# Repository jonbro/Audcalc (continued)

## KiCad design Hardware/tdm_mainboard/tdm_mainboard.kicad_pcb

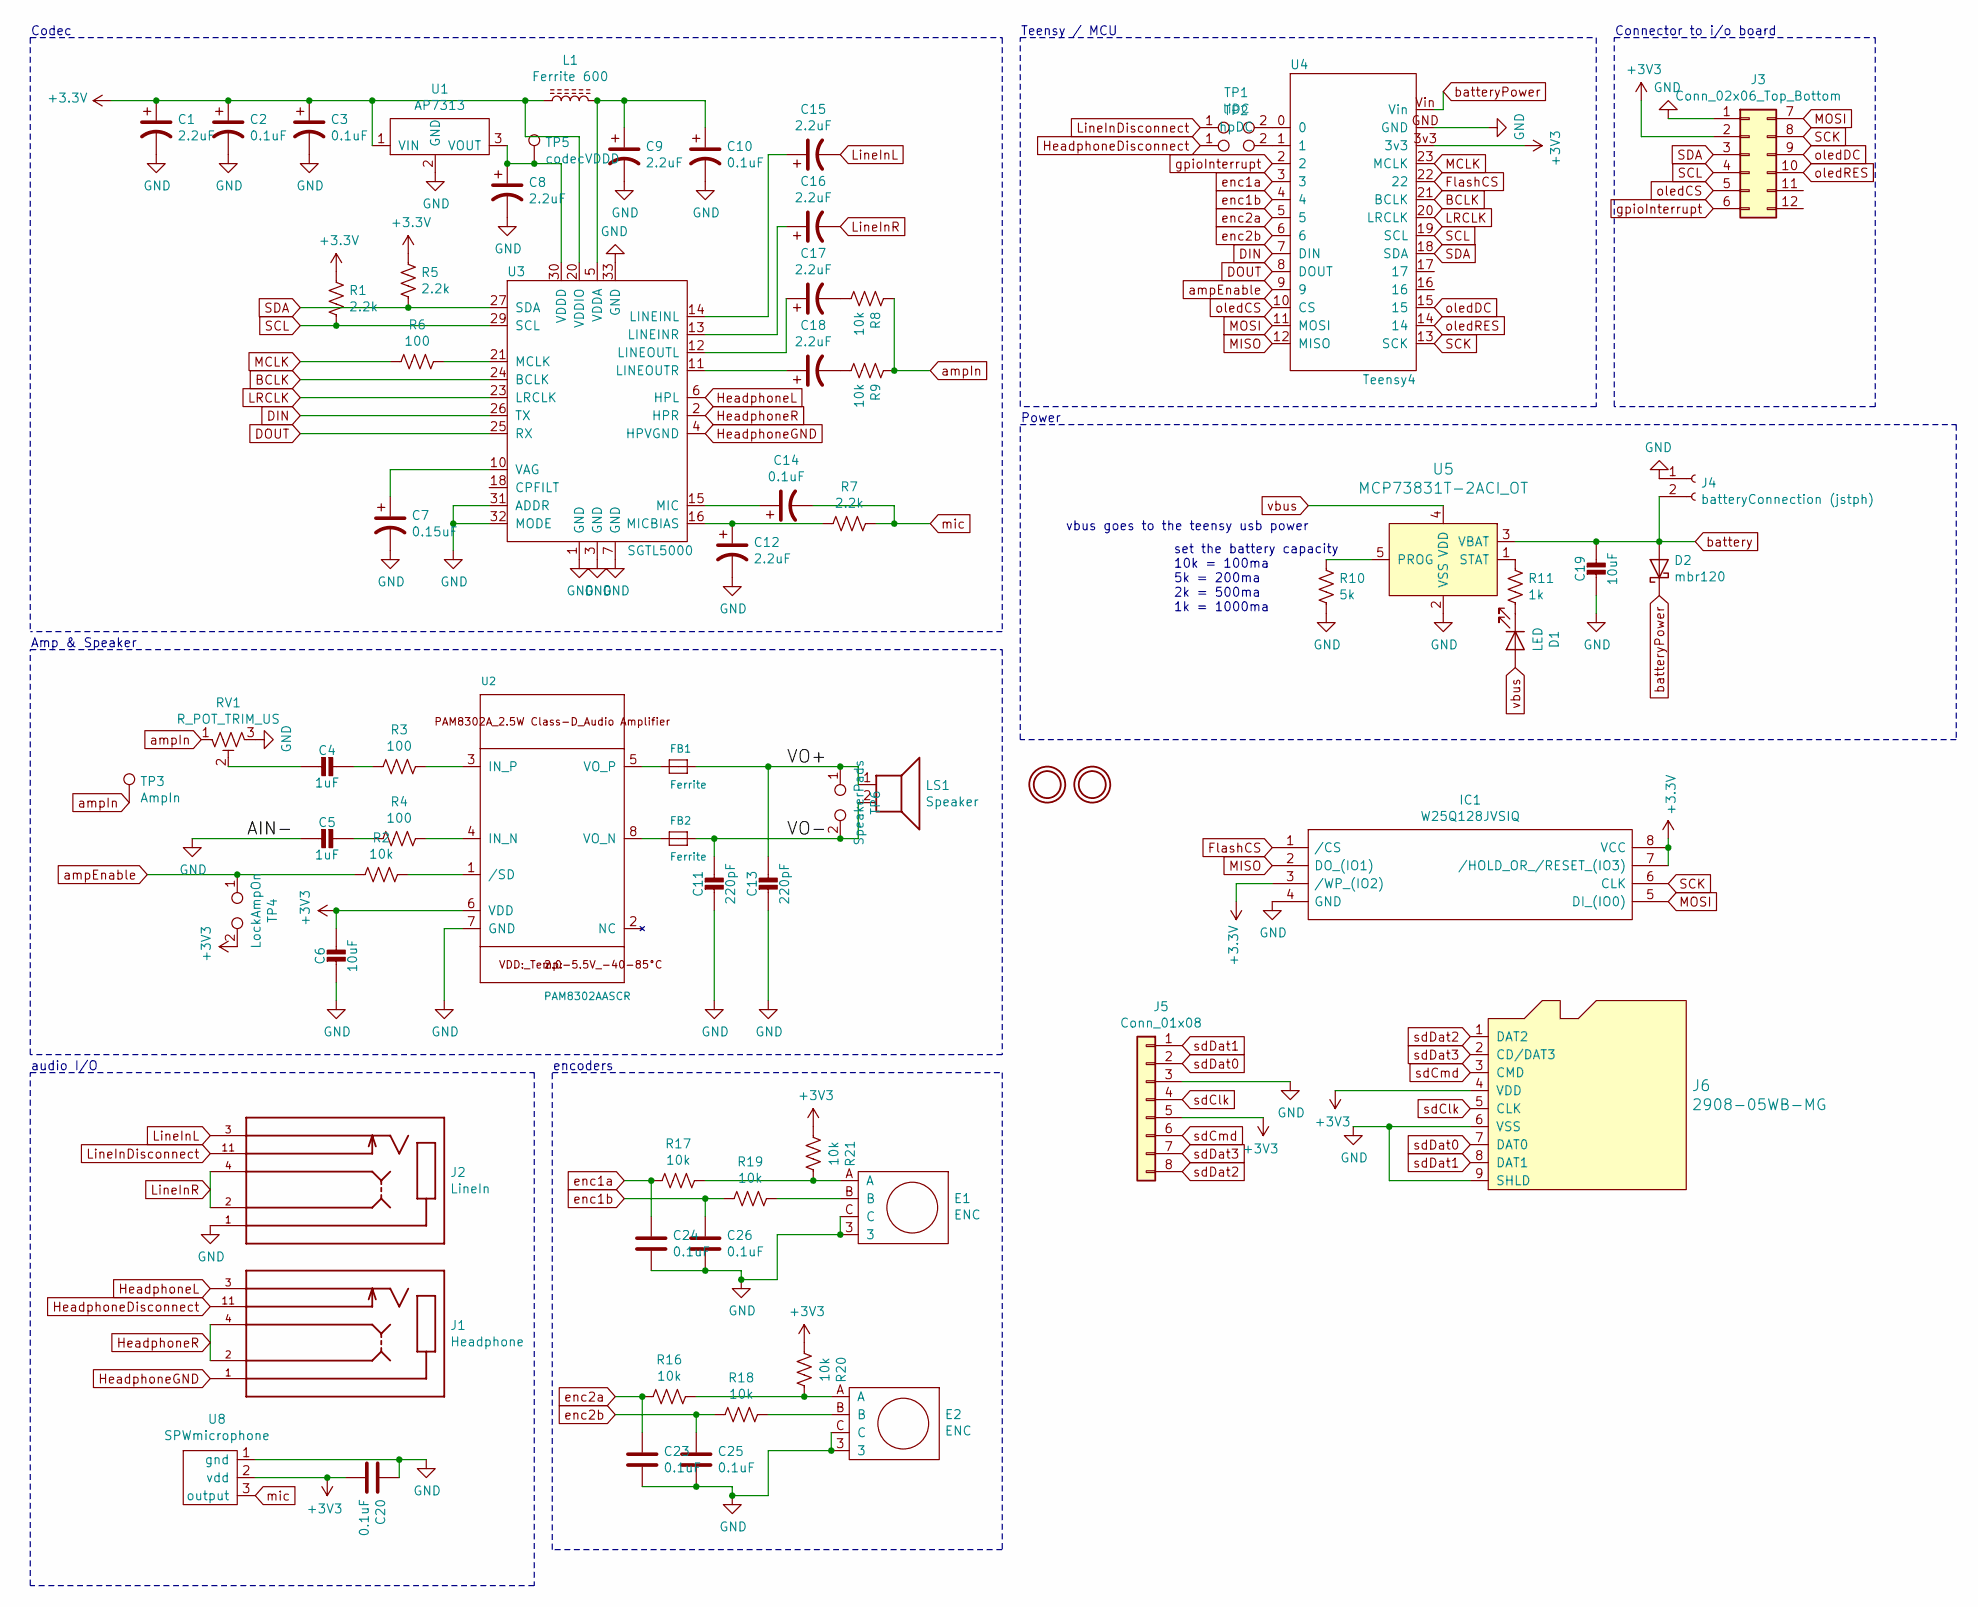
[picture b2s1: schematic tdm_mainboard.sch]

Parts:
C1, C8, C9, C12, C15, C16, C17, C18: 2.2uF; C_0603
C2, C3, C10, C14, C20, C23, C24, C25, C26: 0.1uF; C_0603
C4, C5: 1uF; C_0603
C6, C19: 10uF; C_0603
C7: 0.15uF; C_0603
C11, C13: 220pF; C_0603
D1: LED; LED_0603_HandSoldering
D2: mbr120; D_SOD-123F
E1, E2: ENC; Rotary_Encoder_PEC11R
FB1, FB2: Ferrite; L_0805_HandSoldering
IC1: W25Q128JVSIQ; SOIC127P790X216-8N; Mouser Part Number 454-W25Q128JVSIQ
J1: Headphone; CUI_SJ2-35043C-SMT-TR
J2: LineIn; CUI_SJ2-35043C-SMT-TR
J3: Conn_02x06_Top_Bottom; PinHeader_2x06_P2.54mm_Vertical
J4: batteryConnection (jstph); JST_PH_B2B-PH-K_02x2.00mm_Straight
J5: Conn_01x08; SFW8R-3STE1LF
J6: 2908-05WB-MG; MOLEX_503182-1852_microsd; MPN 2908-05WB-MG; Digi-Key_PN 3M5607CT-ND
L1: Ferrite 600; L_0805_HandSoldering
LS1: Speaker; CMS-18138A-SP
R1, R5, R7: 2.2k; R_0603
R2, R8, R9, R16, R17, R18, R19, R20, R21: 10k; R_0603
R3, R4, R6: 100; R_0603
R10: 5k; R_0603
R11: 1k; R_0603
RV1: R_POT_TRIM_US; TC33X-2_1
TP1: liDC; Test_Point_2Pads
TP2: hpDC; Test_Point_2Pads
TP3: AmpIn; Measurement_Point_Round-TH_Small
TP4: LockAmpOn; Test_Point_2Pads
TP5: codecVDDD; Measurement_Point_Round-SMD-Pad_Small
TP6: SpeakerPads; Test_Point_2Pads
U1: AP7313; SOT-23
U2: PAM8302AASCR; SOP65P490X110-8N
U3: SGTL5000; QFN50P500X500X90-33N
U4: Teensy4
U5: MCP73831T-2ACI_OT; SOT-23-5; MPN MCP73831T-2ACI/OT; Digi-Key_PN MCP73831T-2ACI/OTCT-ND
U6, U7: MOUNTINGHOLE2.5; MountingHole_2.5mm
U8: SPWmicrophone; MIC_SPW2430HR5H-B

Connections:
/VO+: C13.1, FB1.2, LS1.1, TP6.1
/VO-: C11.1, FB2.2, LS1.2, TP6.2
BCLK: U3.24 (BCLK), U4.21 (BCLK)
DIN: U3.26 (TX), U4.7 (DIN)
DOUT: U3.25 (RX), U4.8 (DOUT)
FlashCS: IC1.1 (/CS), U4.22
GND: C1.2, C2.2, C3.2, C5.2, C6.2, C7.2, C8.2, C9.2, C10.2, C11.2, C12.2, C13.2, C19.2, C20.1, C23.2, C24.2, C25.2, C26.2, E1.3, E1.C, E2.3, E2.C, IC1.4 (GND), J2.1 (SLEEVE), J3.1, J4.1, J5.3, J6.6 (VSS), J6.9 (SHLD), R10.2, RV1.3, U1.2 (GND), U2.7 (GND), U3.1 (GND), U3.3 (GND), U3.7 (GND), U3.31 (ADDR), U3.32 (MODE), U3.33 (GND), U4.GND, U5.2 (VSS), U8.1 (gnd)
HeadphoneDisconnect: J1.11 (RING_SWITCH), TP2.1
HeadphoneGND: J1.1 (SLEEVE), U3.4 (HPVGND)
HeadphoneL: J1.3 (RING), U3.6 (HPL)
HeadphoneR: J1.2 (TIP_1), J1.4 (TIP_2), U3.2 (HPR)
LRCLK: U3.23 (LRCLK), U4.20 (LRCLK)
LineInDisconnect: J2.11 (RING_SWITCH), TP1.1
LineInL: C15.2, J2.3 (RING)
LineInR: C16.2, J2.2 (TIP_1), J2.4 (TIP_2)
MCLK: R6.2, U4.23 (MCLK)
MISO: IC1.2 (DO_(IO1)), U4.12 (MISO)
MOSI: IC1.5 (DI_(IO0)), J3.7, U4.11 (MOSI)
unnamed: C4.1, R3.2
unnamed: C4.2, RV1.2
unnamed: C5.1, R4.2
unnamed: C7.1, U3.10 (VAG)
unnamed: C8.1, TP5.1, U1.3 (VOUT), U3.30 (VDDD)
unnamed: C9.1, C10.1, L1.2, U3.5 (VDDA)
unnamed: C12.1, R7.2, U3.16 (MICBIAS)
unnamed: C14.1, U3.15 (MIC)
unnamed: C15.1, U3.14 (LINEINL)
unnamed: C16.1, U3.13 (LINEINR)
unnamed: C17.1, U3.12 (LINEOUTL)
unnamed: C17.2, R8.2
unnamed: C18.1, U3.11 (LINEOUTR)
unnamed: C18.2, R9.2
unnamed: D1.1 (K), R11.2
unnamed: E1.A, R17.1, R21.1
unnamed: E1.B, R19.1
unnamed: E2.A, R16.1, R20.1
unnamed: E2.B, R18.1
unnamed: FB1.1, U2.5 (VO_P)
unnamed: FB2.1, U2.8 (VO_N)
unnamed: R2.1, U2.1 (/SD)
unnamed: R3.1, U2.3 (IN_P)
unnamed: R4.1, U2.4 (IN_N)
unnamed: R6.1, U3.21 (MCLK)
unnamed: R10.1, U5.5 (PROG)
unnamed: R11.1, U5.1 (STAT)
unnamed: TP1.2, U4.0
unnamed: TP2.2, U4.1
SCK: IC1.6 (CLK), J3.8, U4.13 (SCK)
SCL: J3.4, R1.2, U3.29 (SCL), U4.19 (SCL)
SDA: J3.3, R5.2, U3.27 (SDA), U4.18 (SDA)
ampEnable: R2.2, TP4.1, U4.9
ampIn: R8.1, R9.1, RV1.1, TP3.1
battery: C19.1, D2.2 (A), J4.2, U5.3 (VBAT)
batteryPower: D2.1 (K), U4.Vin
enc1a: C24.1, R17.2, U4.3
enc1b: C26.1, R19.2, U4.4
enc2a: C23.1, R16.2, U4.5
enc2b: C25.1, R18.2, U4.6
gpioInterrupt: J3.6, U4.2
mic: C14.2, R7.1, U8.3 (output)
oledCS: J3.5, U4.10 (CS)
oledDC: J3.9, U4.15
oledRES: J3.10, U4.14
sdClk: J5.4, J6.5 (CLK)
sdCmd: J5.6, J6.3 (CMD)
sdDat0: J5.2, J6.7 (DAT0)
sdDat1: J5.1, J6.8 (DAT1)
sdDat2: J5.8, J6.1 (DAT2)
sdDat3: J5.7, J6.2 (CD/DAT3)
vbus: D1.2 (A), U5.4 (VDD)

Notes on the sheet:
Power
Amp & Speaker
Codec
audio I/O
encoders
Teensy / MCU
Connector to i/o board
vbus goes to the teensy usb power
set the battery capacity 10k = 100ma 5k = 200ma 2k = 500ma 1k = 1000ma

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
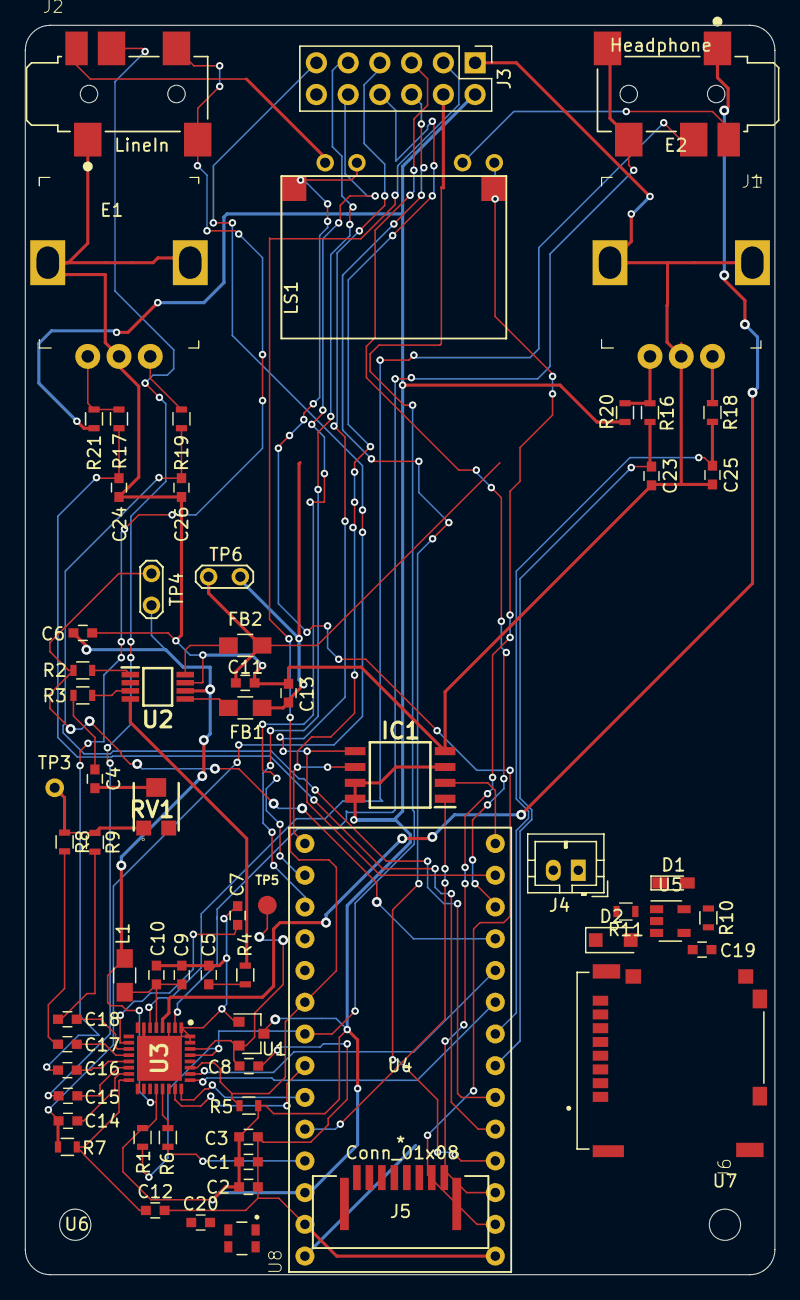
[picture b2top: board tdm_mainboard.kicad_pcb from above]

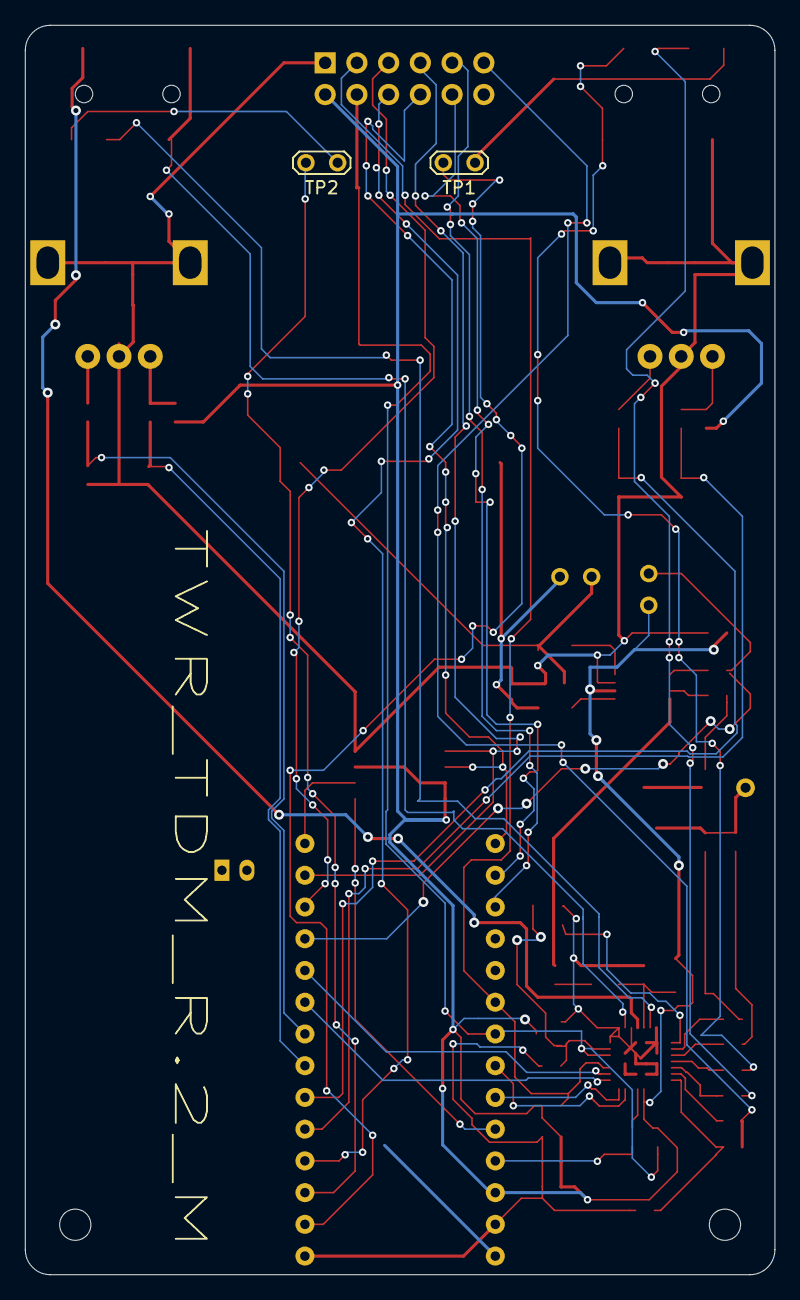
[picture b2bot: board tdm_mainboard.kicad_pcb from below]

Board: 2 copper layers, 60.0 x 100.0 mm, 71 parts (2 on the bottom side), 71 nets.

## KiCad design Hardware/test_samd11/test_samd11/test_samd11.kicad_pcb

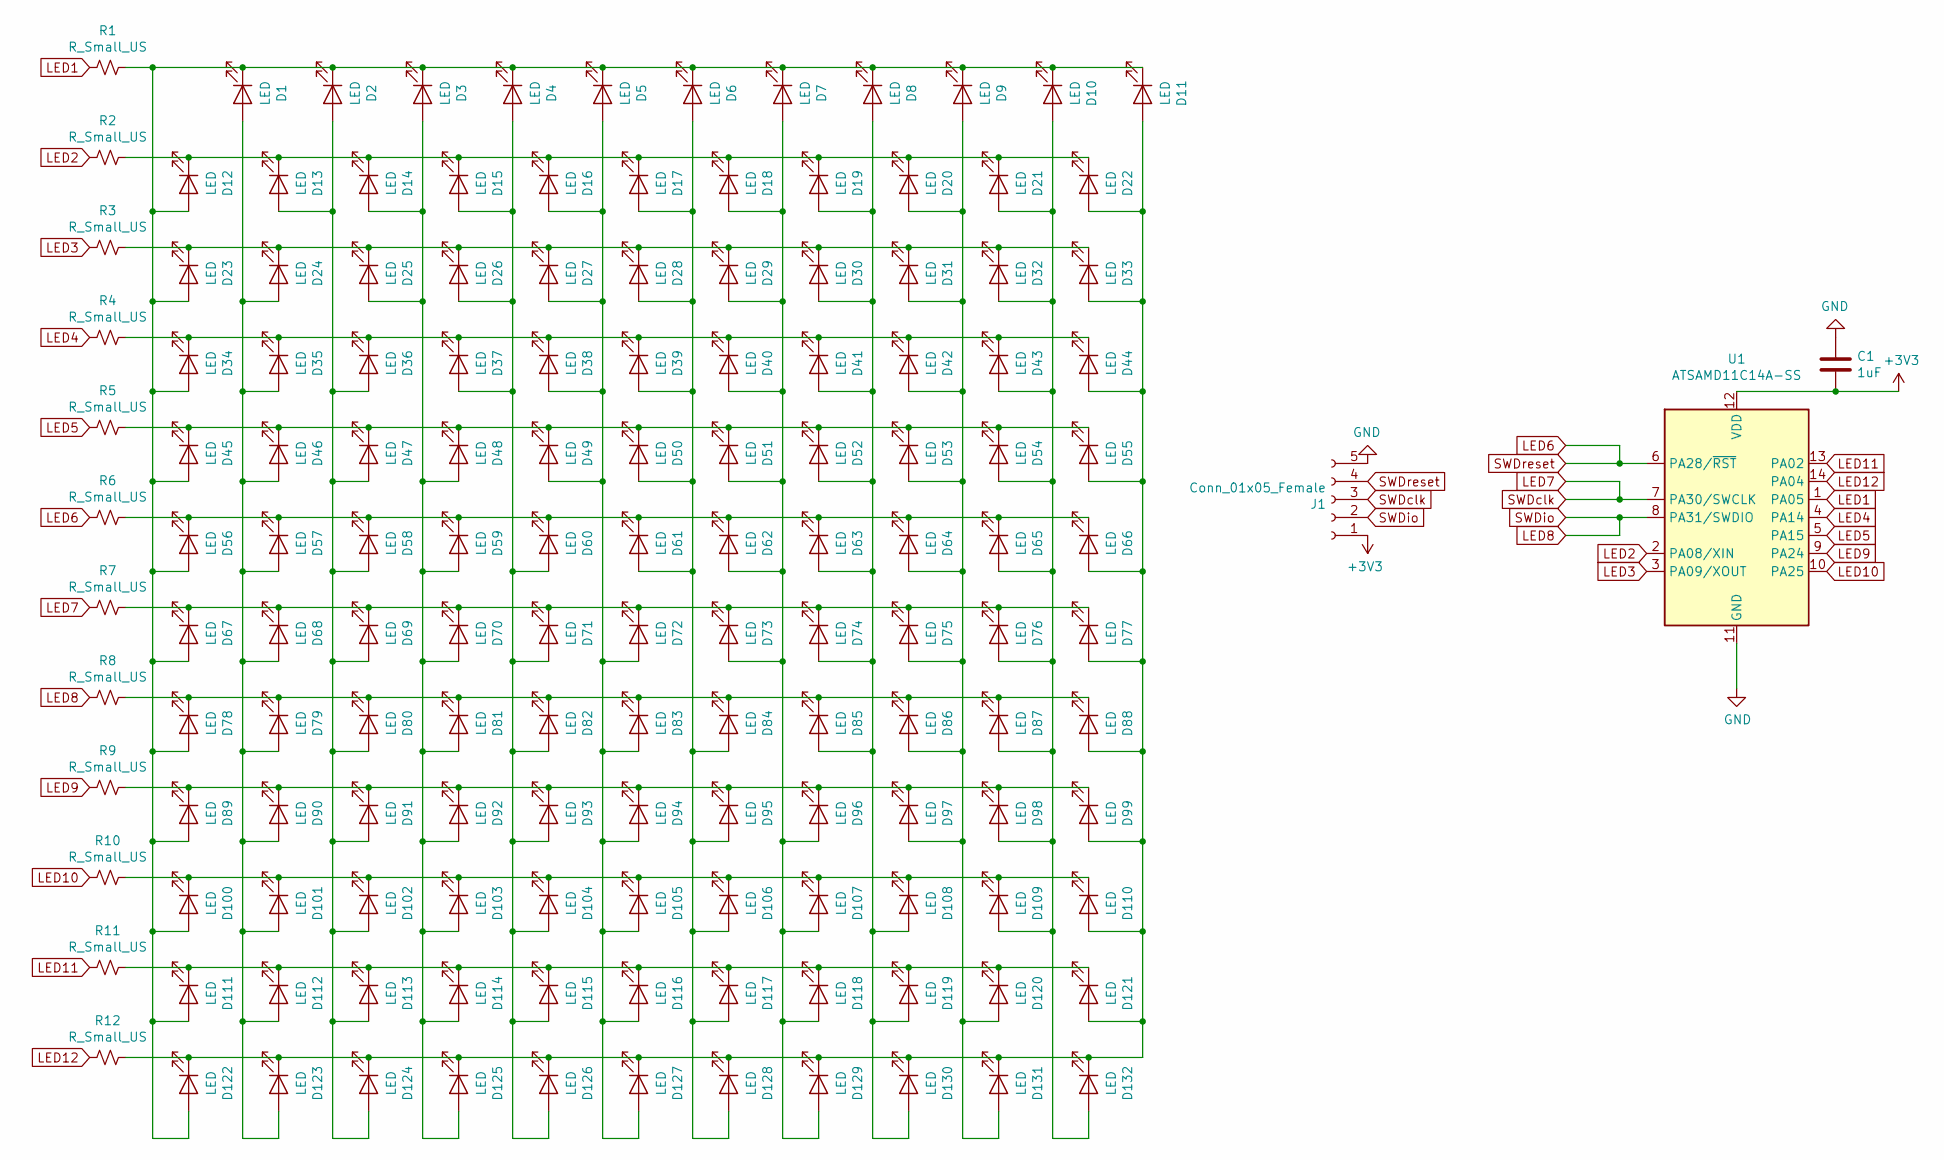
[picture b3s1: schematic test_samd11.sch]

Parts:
C1: 1uF; C_0603
D1, D2, D3, D4, D5, D6, D7, D8, D9, D10, D11, D12, D13, D14, D15, D16, D17, D18, D19, D20, D21, D22, D23, D24, D25, D26, D27, D28, D29, D30, D31, D32, D33, D34, D35, D36, D37, D38, D39, D40, D41, D42, D43, D44, D45, D46, D47, D48, D49, D50, D51, D52, D53, D54, D55, D56, D57, D58, D59, D60, D61, D62, D63, D64, D65, D66, D67, D68, D69, D70, D71, D72, D73, D74, D75, D76, D77, D78, D79, D80, D81, D82, D83, D84, D85, D86, D87, D88, D89, D90, D91, D92, D93, D94, D95, D96, D97, D98, D99, D100, D101, D102, D103, D104, D105, D106, D107, D108, D109, D110, D111, D112, D113, D114, D115, D116, D117, D118, D119, D120, D121, D122, D123, D124, D125, D126, D127, D128, D129, D130, D131, D132: LED; D_0603
J1: Conn_01x05_Female; PinSocket_1x05_P2.54mm_Vertical
R1, R2, R3, R4, R5, R6, R7, R8, R9, R10, R11, R12: R_Small_US; R_0603
U1: ATSAMD11C14A-SS; SOIC-14_N

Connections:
+3V3: C1.2, J1.1, U1.12 (VDD)
GND: C1.1, J1.5, U1.11 (GND)
LED1: R1.2, U1.1 (PA05)
LED2: R2.2, U1.2 (PA08/XIN)
LED3: R3.2, U1.3 (PA09/XOUT)
LED4: R4.2, U1.4 (PA14)
LED5: R5.2, U1.5 (PA15)
LED6: J1.4, R6.2, U1.6 (PA28/~RST)
LED7: J1.3, R7.2, U1.7 (PA30/SWCLK)
LED8: J1.2, R8.2, U1.8 (PA31/SWDIO)
LED9: R9.2, U1.9 (PA24)
LED10: R10.2, U1.10 (PA25)
LED11: R11.2, U1.13 (PA02)
LED12: R12.2, U1.14 (PA04)
unnamed: D1.1 (K), D2.1 (K), D3.1 (K), D4.1 (K), D5.1 (K), D6.1 (K), D7.1 (K), D8.1 (K), D9.1 (K), D10.1 (K), D11.1 (K), D12.2 (A), D23.2 (A), D34.2 (A), D45.2 (A), D56.2 (A), D67.2 (A), D78.2 (A), D89.2 (A), D100.2 (A), D111.2 (A), D122.2 (A), R1.1
unnamed: D1.2 (A), D24.2 (A), D35.2 (A), D46.2 (A), D57.2 (A), D68.2 (A), D79.2 (A), D90.2 (A), D101.2 (A), D112.2 (A), D123.2 (A)
unnamed: D10.2 (A), D21.2 (A), D32.2 (A), D43.2 (A), D54.2 (A), D65.2 (A), D76.2 (A), D87.2 (A), D98.2 (A), D109.2 (A), D132.2 (A)
unnamed: D11.2 (A), D22.2 (A), D33.2 (A), D44.2 (A), D55.2 (A), D66.2 (A), D77.2 (A), D88.2 (A), D99.2 (A), D110.2 (A), D121.2 (A), D122.1 (K), D123.1 (K), D124.1 (K), D125.1 (K), D126.1 (K), D127.1 (K), D128.1 (K), D129.1 (K), D130.1 (K), D131.1 (K), D132.1 (K), R12.1
unnamed: D12.1 (K), D13.1 (K), D14.1 (K), D15.1 (K), D16.1 (K), D17.1 (K), D18.1 (K), D19.1 (K), D20.1 (K), D21.1 (K), D22.1 (K), R2.1
unnamed: D23.1 (K), D24.1 (K), D25.1 (K), D26.1 (K), D27.1 (K), D28.1 (K), D29.1 (K), D30.1 (K), D31.1 (K), D32.1 (K), D33.1 (K), R3.1
unnamed: D34.1 (K), D35.1 (K), D36.1 (K), D37.1 (K), D38.1 (K), D39.1 (K), D40.1 (K), D41.1 (K), D42.1 (K), D43.1 (K), D44.1 (K), R4.1
unnamed: D45.1 (K), D46.1 (K), D47.1 (K), D48.1 (K), D49.1 (K), D50.1 (K), D51.1 (K), D52.1 (K), D53.1 (K), D54.1 (K), D55.1 (K), R5.1
unnamed: D56.1 (K), D57.1 (K), D58.1 (K), D59.1 (K), D60.1 (K), D61.1 (K), D62.1 (K), D63.1 (K), D64.1 (K), D65.1 (K), D66.1 (K), R6.1
unnamed: D67.1 (K), D68.1 (K), D69.1 (K), D70.1 (K), D71.1 (K), D72.1 (K), D73.1 (K), D74.1 (K), D75.1 (K), D76.1 (K), D77.1 (K), R7.1
unnamed: D78.1 (K), D79.1 (K), D80.1 (K), D81.1 (K), D82.1 (K), D83.1 (K), D84.1 (K), D85.1 (K), D86.1 (K), D87.1 (K), D88.1 (K), R8.1
unnamed: D89.1 (K), D90.1 (K), D91.1 (K), D92.1 (K), D93.1 (K), D94.1 (K), D95.1 (K), D96.1 (K), D97.1 (K), D98.1 (K), D99.1 (K), R9.1
unnamed: D100.1 (K), D101.1 (K), D102.1 (K), D103.1 (K), D104.1 (K), D105.1 (K), D106.1 (K), D107.1 (K), D108.1 (K), D109.1 (K), D110.1 (K), R10.1
unnamed: D2.2 (A), D13.2 (A), D36.2 (A), D47.2 (A), D58.2 (A), D69.2 (A), D80.2 (A), D91.2 (A), D102.2 (A), D113.2 (A), D124.2 (A)
unnamed: D3.2 (A), D14.2 (A), D25.2 (A), D48.2 (A), D59.2 (A), D70.2 (A), D81.2 (A), D92.2 (A), D103.2 (A), D114.2 (A), D125.2 (A)
unnamed: D4.2 (A), D15.2 (A), D26.2 (A), D37.2 (A), D60.2 (A), D71.2 (A), D82.2 (A), D93.2 (A), D104.2 (A), D115.2 (A), D126.2 (A)
unnamed: D5.2 (A), D16.2 (A), D27.2 (A), D38.2 (A), D49.2 (A), D72.2 (A), D83.2 (A), D94.2 (A), D105.2 (A), D116.2 (A), D127.2 (A)
unnamed: D6.2 (A), D17.2 (A), D28.2 (A), D39.2 (A), D50.2 (A), D61.2 (A), D84.2 (A), D95.2 (A), D106.2 (A), D117.2 (A), D128.2 (A)
unnamed: D7.2 (A), D18.2 (A), D29.2 (A), D40.2 (A), D51.2 (A), D62.2 (A), D73.2 (A), D96.2 (A), D107.2 (A), D118.2 (A), D129.2 (A)
unnamed: D8.2 (A), D19.2 (A), D30.2 (A), D41.2 (A), D52.2 (A), D63.2 (A), D74.2 (A), D85.2 (A), D108.2 (A), D119.2 (A), D130.2 (A)
unnamed: D111.1 (K), D112.1 (K), D113.1 (K), D114.1 (K), D115.1 (K), D116.1 (K), D117.1 (K), D118.1 (K), D119.1 (K), D120.1 (K), D121.1 (K), R11.1
unnamed: D9.2 (A), D20.2 (A), D31.2 (A), D42.2 (A), D53.2 (A), D64.2 (A), D75.2 (A), D86.2 (A), D97.2 (A), D120.2 (A), D131.2 (A)

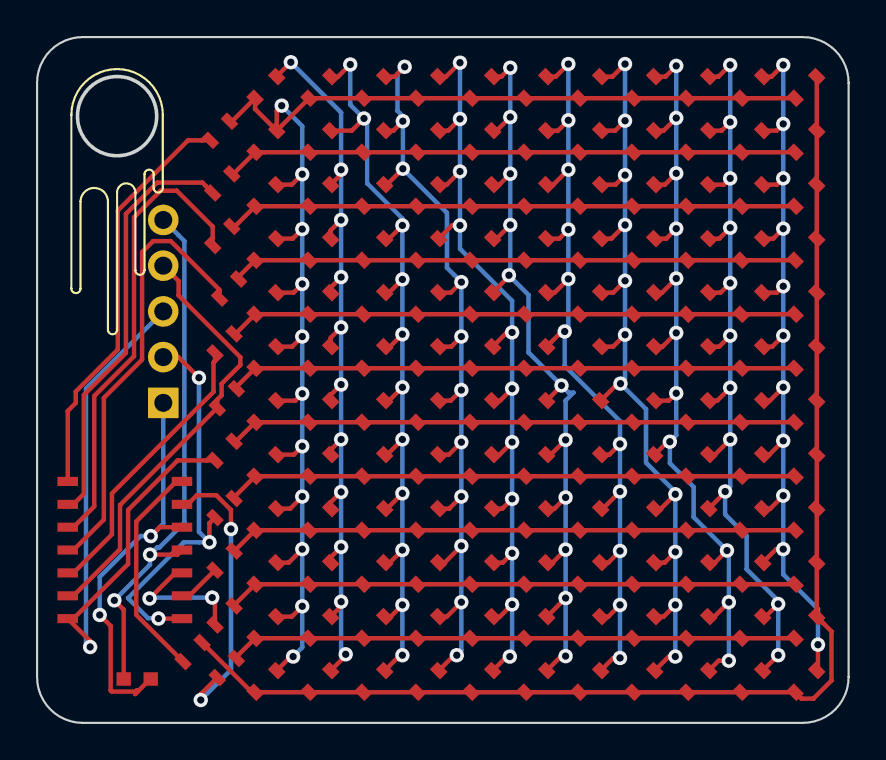
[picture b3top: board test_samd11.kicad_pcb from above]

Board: 2 copper layers, 45.0 x 38.0 mm, 147 parts (0 on the bottom side), 36 nets.

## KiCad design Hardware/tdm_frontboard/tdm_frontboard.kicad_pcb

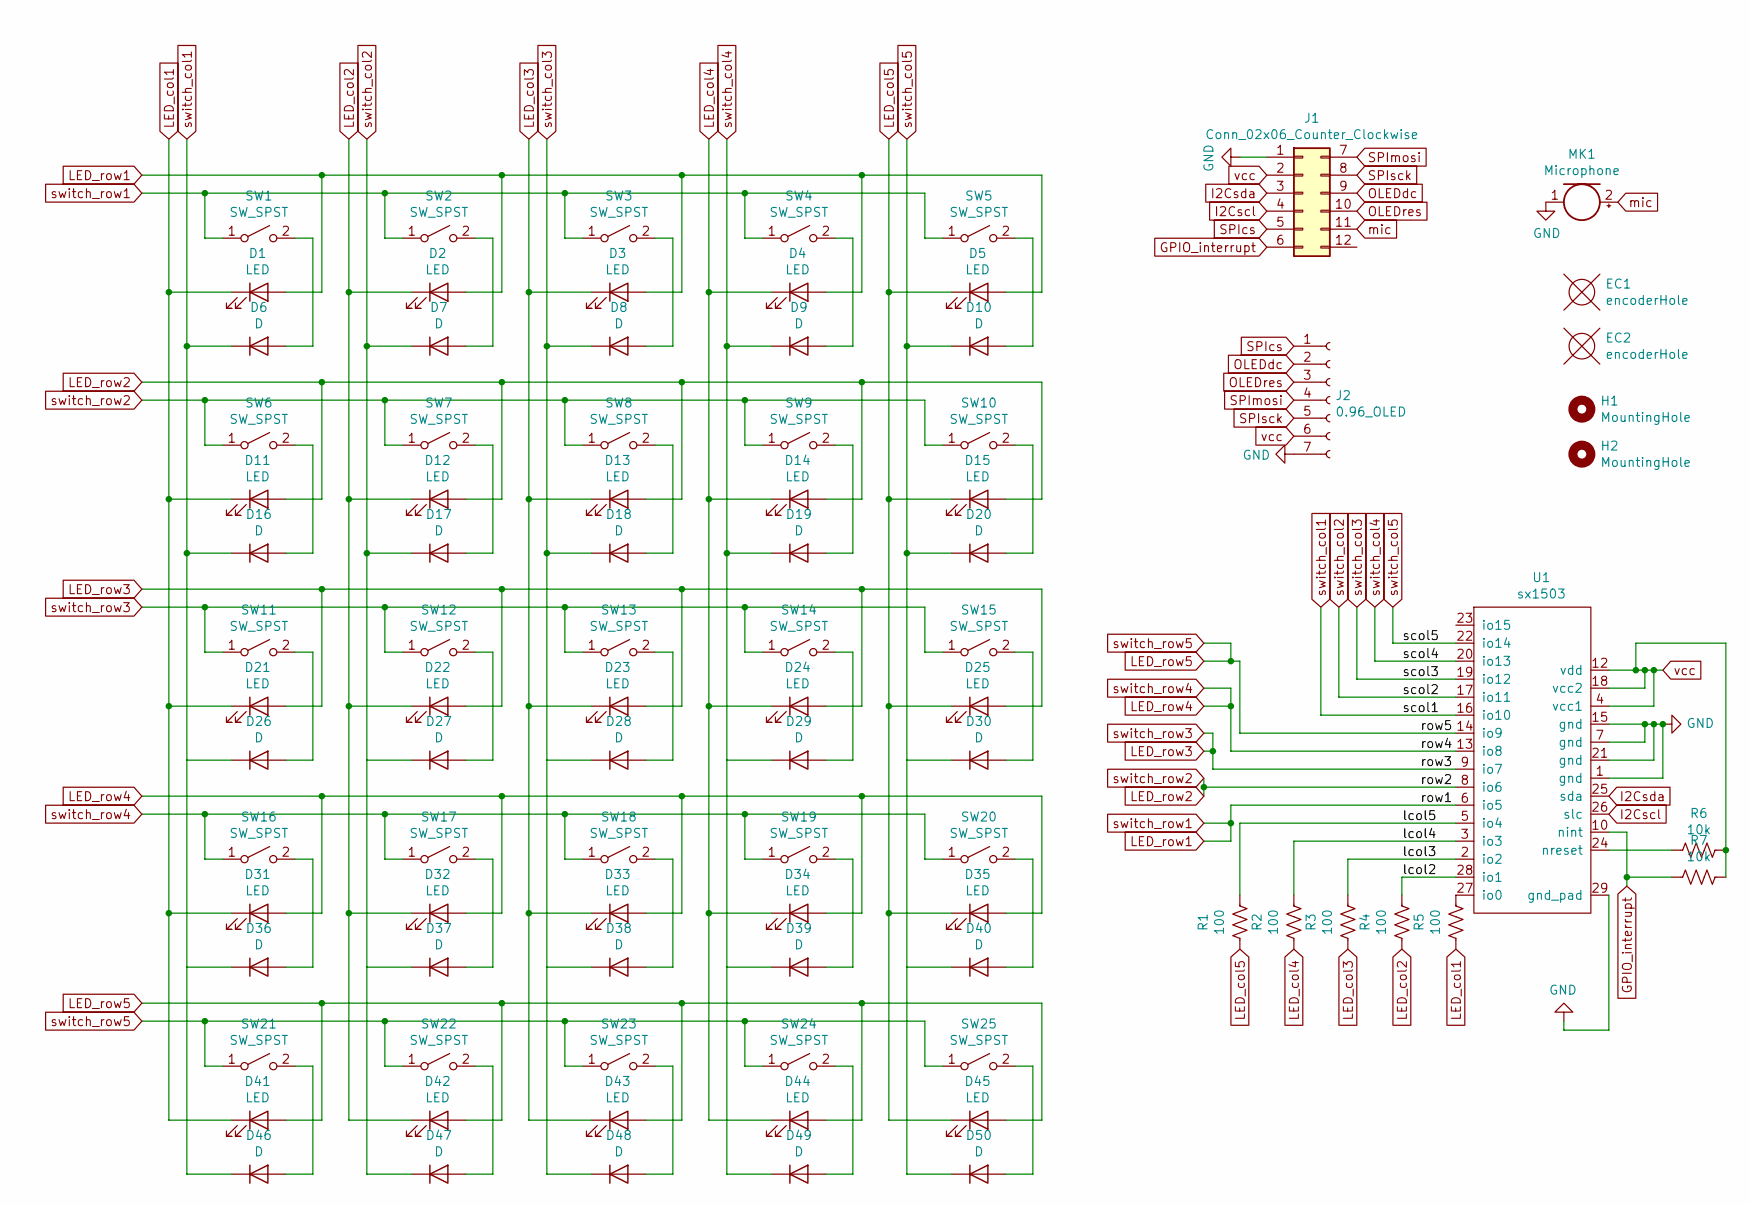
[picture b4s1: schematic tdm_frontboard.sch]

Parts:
D1, D2, D3, D4, D5, D11, D12, D13, D14, D15, D21, D22, D23, D24, D25, D31, D32, D33, D34, D35, D41, D42, D43, D44, D45: LED; LED_0603_HandSoldering
D6, D7, D8, D9, D10, D16, D17, D18, D19, D20, D26, D27, D28, D29, D30, D36, D37, D38, D39, D40, D46, D47, D48, D49, D50: D; Diode_0603_HandSoldering
EC1, EC2: encoderHole; ENC_hole
H1, H2: MountingHole; MountingHole_2.5mm
J1: Conn_02x06_Counter_Clockwise; PinHeader_2x06_P2.54mm_Vertical
J2: 0.96_OLED; PinSocket_1x07_P2.54mm_Vertical
MK1: Microphone; Mic_CMA-4544PF-W
R1, R2, R3, R4, R5: 100; R_0603_HandSoldering
R6, R7: 10k; R_0603_HandSoldering
SW1, SW2, SW3, SW4, SW5, SW6, SW7, SW8, SW9, SW10, SW11, SW12, SW13, SW14, SW15, SW16, SW17, SW18, SW19, SW20, SW21, SW22, SW23, SW24, SW25: SW_SPST; TS-023E
U1: sx1503

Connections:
/lcol2: R4.2, U1.28 (io1)
/lcol3: R3.2, U1.2 (io2)
/lcol4: R2.2, U1.3 (io3)
/lcol5: R1.2, U1.5 (io4)
GND: J1.1, J2.7, MK1.1 (-), U1.1 (gnd), U1.7 (gnd), U1.15 (gnd), U1.21 (gnd), U1.29 (gnd_pad)
GPIO_interrupt: J1.6, R7.1, U1.10 (nint)
I2Cscl: J1.4, U1.26 (slc)
I2Csda: J1.3, U1.25 (sda)
LED_col1: D1.1 (K), D11.1 (K), D21.1 (K), D31.1 (K), D41.1 (K), R5.1
LED_col2: D2.1 (K), D12.1 (K), D22.1 (K), D32.1 (K), D42.1 (K), R4.1
LED_col3: D3.1 (K), D13.1 (K), D23.1 (K), D33.1 (K), D43.1 (K), R3.1
LED_col4: D4.1 (K), D14.1 (K), D24.1 (K), D34.1 (K), D44.1 (K), R2.1
LED_col5: D5.1 (K), D15.1 (K), D25.1 (K), D35.1 (K), D45.1 (K), R1.1
LED_row1: D1.2 (A), D2.2 (A), D3.2 (A), D4.2 (A), D5.2 (A), SW1.1 (A), SW2.1 (A), SW3.1 (A), SW4.1 (A), SW5.1 (A), U1.6 (io5)
LED_row2: D11.2 (A), D12.2 (A), D13.2 (A), D14.2 (A), D15.2 (A), SW6.1 (A), SW7.1 (A), SW8.1 (A), SW9.1 (A), SW10.1 (A), U1.8 (io6)
LED_row3: D21.2 (A), D22.2 (A), D23.2 (A), D24.2 (A), D25.2 (A), SW11.1 (A), SW12.1 (A), SW13.1 (A), SW14.1 (A), SW15.1 (A), U1.9 (io7)
LED_row4: D31.2 (A), D32.2 (A), D33.2 (A), D34.2 (A), D35.2 (A), SW16.1 (A), SW17.1 (A), SW18.1 (A), SW19.1 (A), SW20.1 (A), U1.13 (io8)
LED_row5: D41.2 (A), D42.2 (A), D43.2 (A), D44.2 (A), D45.2 (A), SW21.1 (A), SW22.1 (A), SW23.1 (A), SW24.1 (A), SW25.1 (A), U1.14 (io9)
unnamed: D6.2 (A), SW1.2 (B)
unnamed: D7.2 (A), SW2.2 (B)
unnamed: D8.2 (A), SW3.2 (B)
unnamed: D9.2 (A), SW4.2 (B)
unnamed: D10.2 (A), SW5.2 (B)
unnamed: D16.2 (A), SW6.2 (B)
unnamed: D17.2 (A), SW7.2 (B)
unnamed: D18.2 (A), SW8.2 (B)
unnamed: D19.2 (A), SW9.2 (B)
unnamed: D20.2 (A), SW10.2 (B)
unnamed: D26.2 (A), SW11.2 (B)
unnamed: D27.2 (A), SW12.2 (B)
unnamed: D28.2 (A), SW13.2 (B)
unnamed: D29.2 (A), SW14.2 (B)
unnamed: D30.2 (A), SW15.2 (B)
unnamed: D36.2 (A), SW16.2 (B)
unnamed: D37.2 (A), SW17.2 (B)
unnamed: D38.2 (A), SW18.2 (B)
unnamed: D39.2 (A), SW19.2 (B)
unnamed: D40.2 (A), SW20.2 (B)
unnamed: D46.2 (A), SW21.2 (B)
unnamed: D47.2 (A), SW22.2 (B)
unnamed: D48.2 (A), SW23.2 (B)
unnamed: D49.2 (A), SW24.2 (B)
unnamed: D50.2 (A), SW25.2 (B)
unnamed: R5.2, U1.27 (io0)
unnamed: R6.1, U1.24 (nreset)
OLEDdc: J1.9, J2.2
OLEDres: J1.10, J2.3
SPIcs: J1.5, J2.1
SPImosi: J1.7, J2.4
SPIsck: J1.8, J2.5
mic: J1.11, MK1.2 (+)
switch_col1: D6.1 (K), D16.1 (K), D26.1 (K), D36.1 (K), D46.1 (K), U1.16 (io10)
switch_col2: D7.1 (K), D17.1 (K), D27.1 (K), D37.1 (K), D47.1 (K), U1.17 (io11)
switch_col3: D8.1 (K), D18.1 (K), D28.1 (K), D38.1 (K), D48.1 (K), U1.19 (io12)
switch_col4: D9.1 (K), D19.1 (K), D29.1 (K), D39.1 (K), D49.1 (K), U1.20 (io13)
switch_col5: D10.1 (K), D20.1 (K), D30.1 (K), D40.1 (K), D50.1 (K), U1.22 (io14)
vcc: J1.2, J2.6, R6.2, R7.2, U1.4 (vcc1), U1.12 (vdd), U1.18 (vcc2)

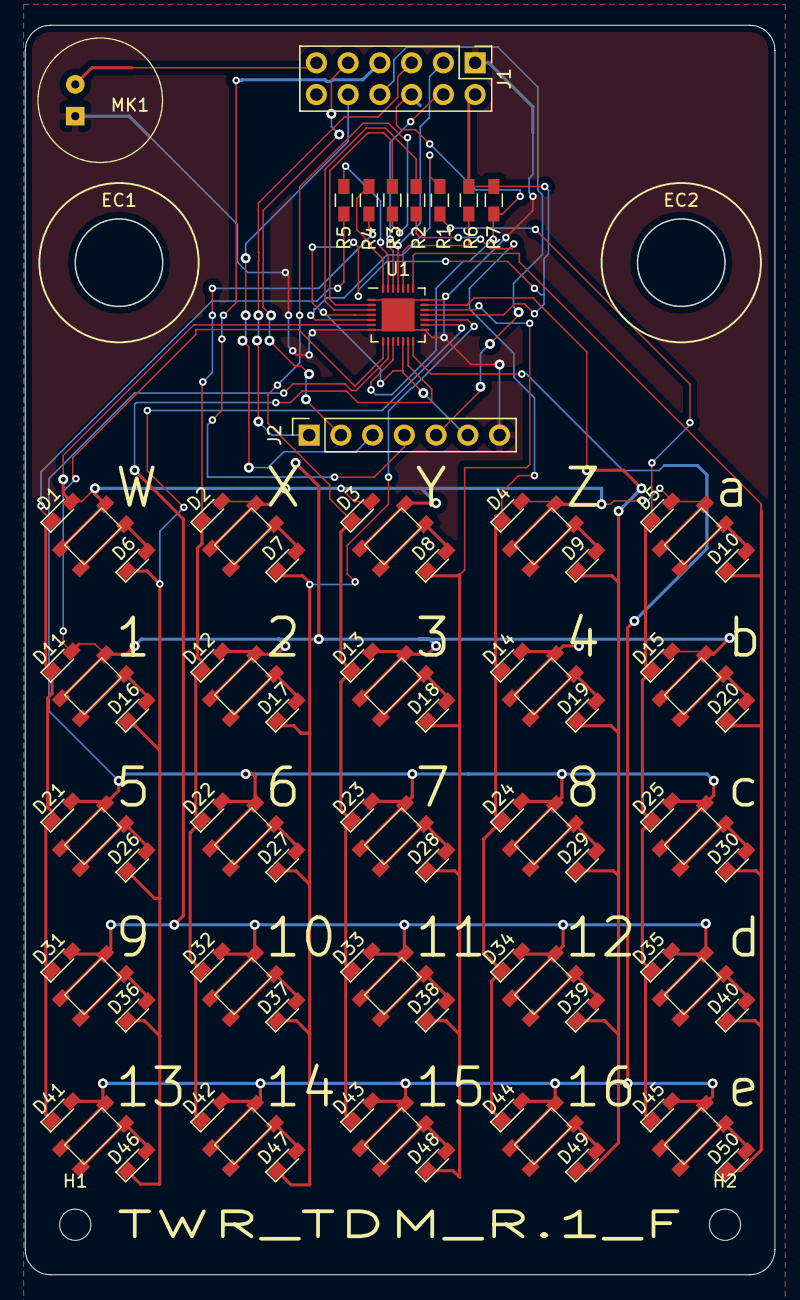
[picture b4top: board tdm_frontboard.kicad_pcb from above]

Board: 2 copper layers, 59.9 x 99.9 mm, 90 parts (0 on the bottom side), 57 nets.

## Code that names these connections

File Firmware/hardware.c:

#include "hardware.h"
#include "ssd1306.h"

#define LINE_IN_DETECT 24
#define HEADPHONE_DETECT 16
#define row_pin_base 11
#define col_pin_base 6
#define BLINK_PIN_LED 25
#define USB_POWER_SENSE 29
#define SUBSYSTEM_RESET_PIN 21

// I2C defines
#define I2C_SDA 2
#define I2C_SCL 3

static bool last_amp_state;
static uint8_t battery_level;
static int8_t lastHpVol = -10; 

i2c_dma_t* i2c_dma;

void hardware_init()
{
    // give all the caps some time to warm up
    sleep_ms(100);
    gpio_init(BLINK_PIN_LED);
    gpio_set_dir(BLINK_PIN_LED, GPIO_OUT);
    // gpio_put(BLINK_PIN_LED, true);
    set_sys_clock_khz(200000, true);

    adc_init();
    adc_gpio_init(26);
    adc_gpio_init(27);
    adc_gpio_init(28);

    gpio_init(USB_POWER_SENSE);
    // in the past I had issues with bad ADC values when this was set to in - keep an eye on this
    gpio_set_dir(USB_POWER_SENSE, GPIO_IN);
    gpio_pull_down(USB_POWER_SENSE);

    // power switch / key 1,1
    gpio_init(23);
    gpio_set_dir(23, GPIO_IN);
    gpio_set_pulls(23, true, false);

    gpio_init(LINE_IN_DETECT);
    gpio_set_dir(LINE_IN_DETECT, GPIO_IN);
    gpio_pull_down(LINE_IN_DETECT);

    gpio_init(HEADPHONE_DETECT);
    gpio_set_dir(HEADPHONE_DETECT, GPIO_IN);
    gpio_pull_up(HEADPHONE_DETECT);

    // setup the rows / colums for input
    for (size_t i = 0; i < 5; i++)
    {
        gpio_init(col_pin_base+i);
        gpio_set_dir(col_pin_base+i, GPIO_OUT);
        gpio_disable_pulls(col_pin_base+i);
        gpio_init(row_pin_base+i);
        gpio_set_dir(row_pin_base+i, GPIO_IN);
        gpio_pull_down(row_pin_base+i);
    }
    
    gpio_init(SUBSYSTEM_RESET_PIN);
    gpio_set_dir(SUBSYSTEM_RESET_PIN, GPIO_OUT);

    gpio_put(SUBSYSTEM_RESET_PIN, 1);
    sleep_ms(10);
    gpio_put(SUBSYSTEM_RESET_PIN, 0);
    sleep_ms(40);
    gpio_put(SUBSYSTEM_RESET_PIN, 1);
    sleep_ms(20);

    gpio_set_function(I2C_SDA, GPIO_FUNC_I2C);
    gpio_set_function(I2C_SCL, GPIO_FUNC_I2C);
    gpio_pull_up(I2C_SDA);
    gpio_pull_up(I2C_SCL);

    // I2C Initialisation. Using it at 400Khz.
    // const int rc = i2c_dma_init(&i2c_dma, I2C_PORT, 400*1000, I2C_SDA, I2C_SCL);
    // gpio_pull_up(I2C_SDA);
    // gpio_pull_up(I2C_SCL);
    i2c_init(I2C_PORT, 400*1000);

    // setup the screen
    ssd1306_t* disp = GetDisplay();
    disp->external_vcc=false;
    ssd1306_init(disp, 128, 32, 0x3C, I2C_PORT);
    ssd1306_poweroff(disp);
    sleep_ms(3);
    ssd1306_poweron(disp);
    ssd1306_clear(disp);
    ssd1306_show(disp);
    ssd1306_contrast(disp, 0x7f); // lower brightness / power requirement

    // gpio_put(BLINK_PIN_LED, false);
}
void hardware_check_i2c_pullups(bool *scl, bool *sda)
{
    gpio_set_function(I2C_SDA, GPIO_FUNC_NULL);
    gpio_set_function(I2C_SCL, GPIO_FUNC_NULL);
    gpio_set_pulls(I2C_SDA, false, false);
    gpio_set_pulls(I2C_SCL, false, false);

    gpio_set_dir(I2C_SDA, GPIO_IN);
    gpio_set_dir(I2C_SCL, GPIO_IN);
    *scl = gpio_get(I2C_SCL);
    *sda = gpio_get(I2C_SDA);

    gpio_set_function(I2C_SDA, GPIO_FUNC_I2C);
    gpio_set_function(I2C_SCL, GPIO_FUNC_I2C);
    gpio_pull_up(I2C_SDA);
    gpio_pull_up(I2C_SCL);
    i2c_init(I2C_PORT, 400*1000);

}
void hardware_reboot_usb()
{
    reset_usb_boot(1<<BLINK_PIN_LED, 0);
}

i2c_dma_t* hardware_get_i2c()
{
    return i2c_dma;
}

bool hardware_get_key_state(uint8_t x, uint8_t y)
{
    if(x==0&&y==0)
        return !gpio_get(23);
    gpio_put_masked(0x7c0, 1<<(col_pin_base+x));
    sleep_us(2);
    return gpio_get(row_pin_base+y);
}

void hardware_get_all_key_state(uint32_t *keyState)
{
    gpio_put(col_pin_base, true);
    // read keys
    for (size_t i = 0; i < 5; i++)
    {
        // the mask here are the gpio pins for the colums
        gpio_put_masked(0x7c0, 1<<(col_pin_base+i));
        sleep_us(1);
        for (size_t j = 0; j < 5; j++)
        {
            int index = (i*5+j);
            bool keyVal = index==0?!gpio_get(23):gpio_get(j+row_pin_base);
            if(keyVal)
            {
                *keyState |= 1ul << index;
            }
            else
            {
                *keyState &= ~(1ul << index);
            }
        }
    }
}

uint8_t hardware_get_battery_level()
{
    return battery_level;
}

void hardware_update_battery_level()
{
    adc_select_input(2);
    battery_level = adc_read()>>4;
}
float hardware_get_battery_level_float()
{
    // 2.33 is voltage divider r1+r2/r2, or in this case 1m+750k/750k or 2.33f
    const float conversion_factor = 2.5f / (1 << 8) * 2.33f;
    // battery level is an int between 0-0xff representing 0-2.5v
    return battery_level * conversion_factor;
}
bool hardware_has_usb_power()
{
    bool res = gpio_get(USB_POWER_SENSE);
    // gpio_put(BLINK_PIN_LED, res);
    return res;
}

void hardware_shutdown()
{
    // shutdown all subsystems
    gpio_put(SUBSYSTEM_RESET_PIN, 0);

    // clear led colors
    uint32_t color[20] = {0};
    memset(color, 0, 20 * sizeof(uint32_t));
    ws2812_setColors(color);
    ws2812_trigger();

    // wait for the powerkey to go low, then shutdown
    while(hardware_get_key_state(0,0))
    {
        // do nothing
    }
    watchdog_enable(1,true);
    while(1);
}
bool hardware_disable_power_latch()
{
    gpio_set_pulls(23, false, false);
}

static bool last_mic_state = false;

void hardware_set_mic(bool mic_state)
{
    if(last_mic_state != mic_state)
    {
        last_mic_state = mic_state;
        driver_set_mic(last_mic_state);
    }
}
void hardware_set_hpvol(int8_t hpVol)
{
    if(lastHpVol != hpVol)
    {
        lastHpVol = hpVol;
        driver_set_hpvol(lastHpVol);
    }
}
bool hardware_line_in_detected()
{
    return !gpio_get(LINE_IN_DETECT);
}
bool hardware_headphone_detected()
{
    return !gpio_get(HEADPHONE_DETECT);
}
